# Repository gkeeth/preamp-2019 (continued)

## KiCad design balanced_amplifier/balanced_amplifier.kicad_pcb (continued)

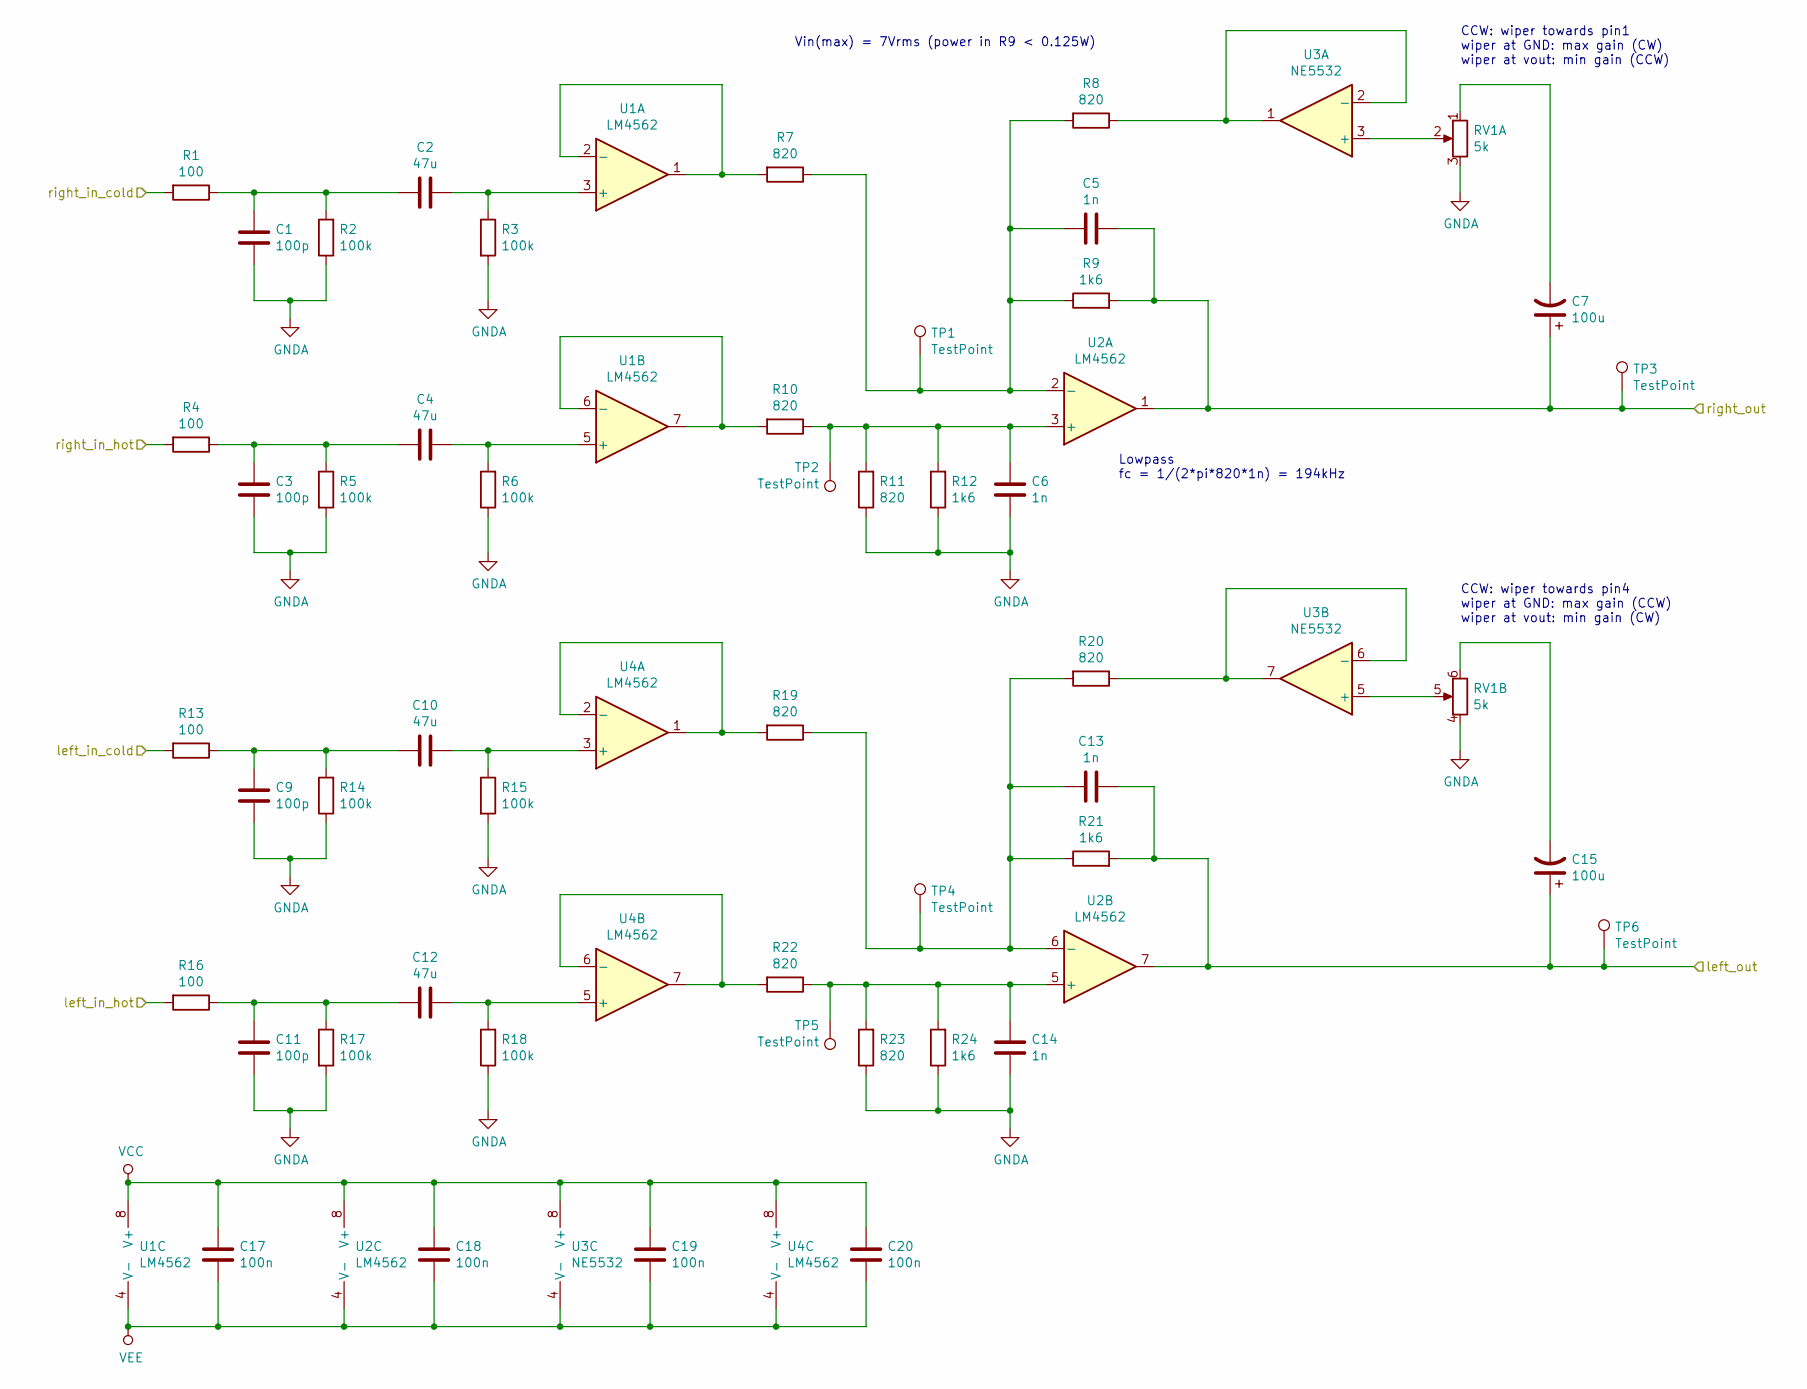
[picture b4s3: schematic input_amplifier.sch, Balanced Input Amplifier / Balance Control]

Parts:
C1, C3, C9, C11: 100p; C_0603_1608Metric_Pad1.05x0.95mm_HandSolder; Manufacturer PN CC0603JRNPO9BN101
C2, C4, C10, C12: 47u; C_Radial_D8.0mm_H11.5mm_P3.50mm; Voltage Rating 35V; Manufacturer PN UVP1V470MPD
C5, C6, C13, C14: 1n; C_0603_1608Metric_Pad1.05x0.95mm_HandSolder; Manufacturer PN GRM1885C1H102FA01J
C7, C15: 100u; CP_Radial_D6.3mm_P2.50mm; Voltage Rating 35V; Manufacturer PN UVR1V101MED
C17, C18, C19, C20: 100n; C_0805_2012Metric_Pad1.15x1.40mm_HandSolder; Manufacturer PN GCM21BR72A104KA37K
R1, R4, R13, R16: 100; R_0603_1608Metric_Pad1.05x0.95mm_HandSolder; Manufacturer PN RT0603FRE07100RL
R2, R3, R5, R6, R14, R15, R17, R18: 100k; R_0603_1608Metric_Pad1.05x0.95mm_HandSolder; Manufacturer PN AT0603DRD07100KL
R7, R8, R10, R11, R19, R20, R22, R23: 820; R_0603_1608Metric_Pad1.05x0.95mm_HandSolder; Manufacturer PN ERA-3AEB821V
R9, R12, R21, R24: 1k6; R_1206_3216Metric_Pad1.42x1.75mm_HandSolder; Manufacturer PN ERA-8AEB162V
RV1: 5k; Potentiometer_Bourns_91A2x-x28-xxx_Dual_Horizontal; Manufacturer PN 91A2A-B28-B13/B13L
TP1, TP2, TP3, TP4, TP5, TP6: TestPoint; TestPoint_Keystone_5000-5004_Miniature; Manufacturer PN 5002
U1, U2, U4: LM4562; SOIC-8_3.9x4.9mm_P1.27mm; Manufacturer PN LM4562MAX/NOPB
U3: NE5532; SOIC-8_3.9x4.9mm_P1.27mm; Manufacturer PN NE5532AD8R2G

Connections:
/left_in_cold: R13.2; also elsewhere on the board
/left_in_hot: R16.2; also elsewhere on the board
/right_in_cold: R1.2; also elsewhere on the board
/right_in_hot: R4.2; also elsewhere on the board
/volume_control/left_in: C13.1, C15.1, R21.2, TP6.1, U2.7; also elsewhere on the board
/volume_control/right_in: C5.1, C7.1, R9.2, TP3.1, U2.1; also elsewhere on the board
GNDA: C1.2, C3.2, C6.2, C9.2, C11.2, C14.2, R2.1, R3.2, R5.2, R6.1, R11.1, R12.1, R14.1, R15.2, R17.2, R18.1, R23.1, R24.1, RV1.3, RV1.4; also elsewhere on the board
unnamed: C1.1, C2.2, R1.1, R2.2
unnamed: C2.1, R3.1, U1.3 (+)
unnamed: C3.1, C4.2, R4.1, R5.1
unnamed: C4.1, R6.2, U1.5 (+)
unnamed: C5.2, R7.1, R8.2, R9.1, TP1.1, U2.2 (-)
unnamed: C6.1, R10.1, R11.2, R12.2, TP2.1, U2.3 (+)
unnamed: C7.2, RV1.1
unnamed: C10.1, R15.1, U4.3 (+)
unnamed: C9.1, C10.2, R13.1, R14.2
unnamed: C11.1, C12.2, R16.1, R17.1
unnamed: C12.1, R18.2, U4.5 (+)
unnamed: C13.2, R19.1, R20.2, R21.1, TP4.1, U2.6 (-)
unnamed: C14.1, R22.1, R23.2, R24.2, TP5.1, U2.5 (+)
unnamed: C15.2, RV1.6
unnamed: R7.2, U1.1, U1.2 (-)
unnamed: R8.1, U3.1, U3.2 (-)
unnamed: R10.2, U1.6 (-), U1.7
unnamed: R19.2, U4.1, U4.2 (-)
unnamed: R20.1, U3.6 (-), U3.7
unnamed: R22.2, U4.6 (-), U4.7
unnamed: RV1.2, U3.3 (+)
unnamed: RV1.5, U3.5 (+)
VCC: C17.1, C18.1, C19.1, C20.1, U1.8 (V+), U2.8 (V+), U3.8 (V+), U4.8 (V+); also elsewhere on the board
VEE: C17.2, C18.2, C19.2, C20.2, U1.4 (V-), U2.4 (V-), U3.4 (V-), U4.4 (V-); also elsewhere on the board

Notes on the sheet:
Lowpass fc = 1/(2*pi*820*1n) = 194kHz
CCW: wiper towards pin1 wiper at GND: max gain (CW) wiper at vout: min gain (CCW)
CCW: wiper towards pin4 wiper at GND: max gain (CCW) wiper at vout: min gain (CW)
Vin(max) = 7Vrms (power in R9 < 0.125W)

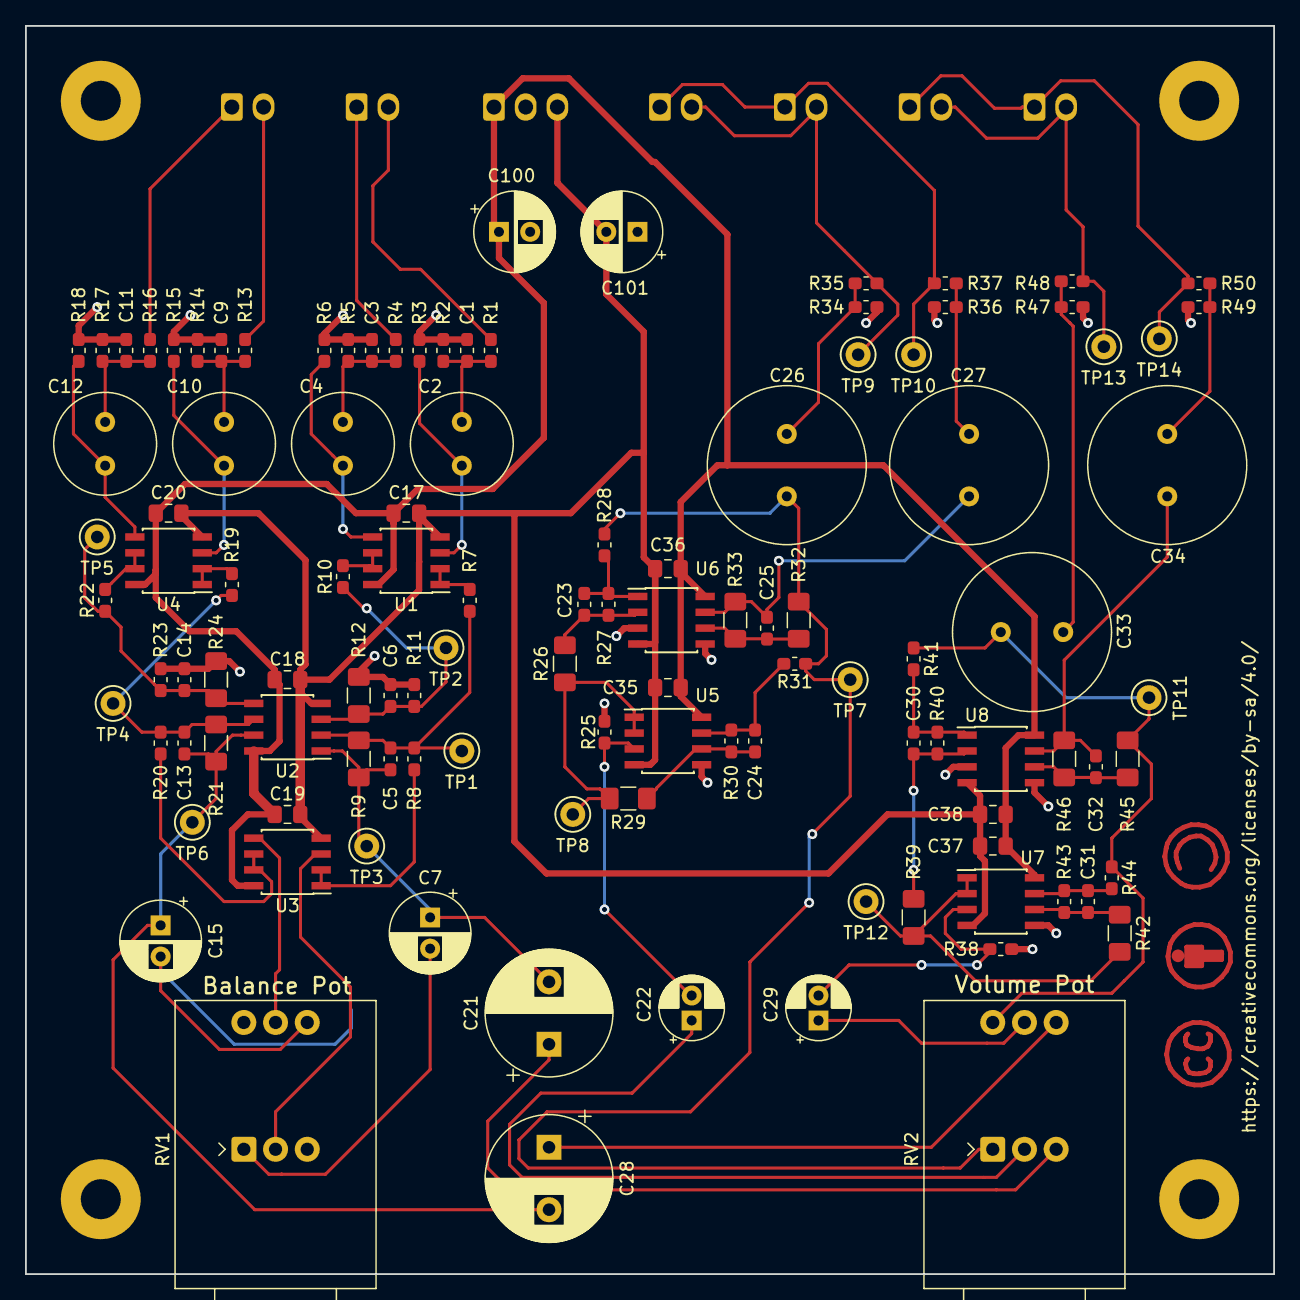
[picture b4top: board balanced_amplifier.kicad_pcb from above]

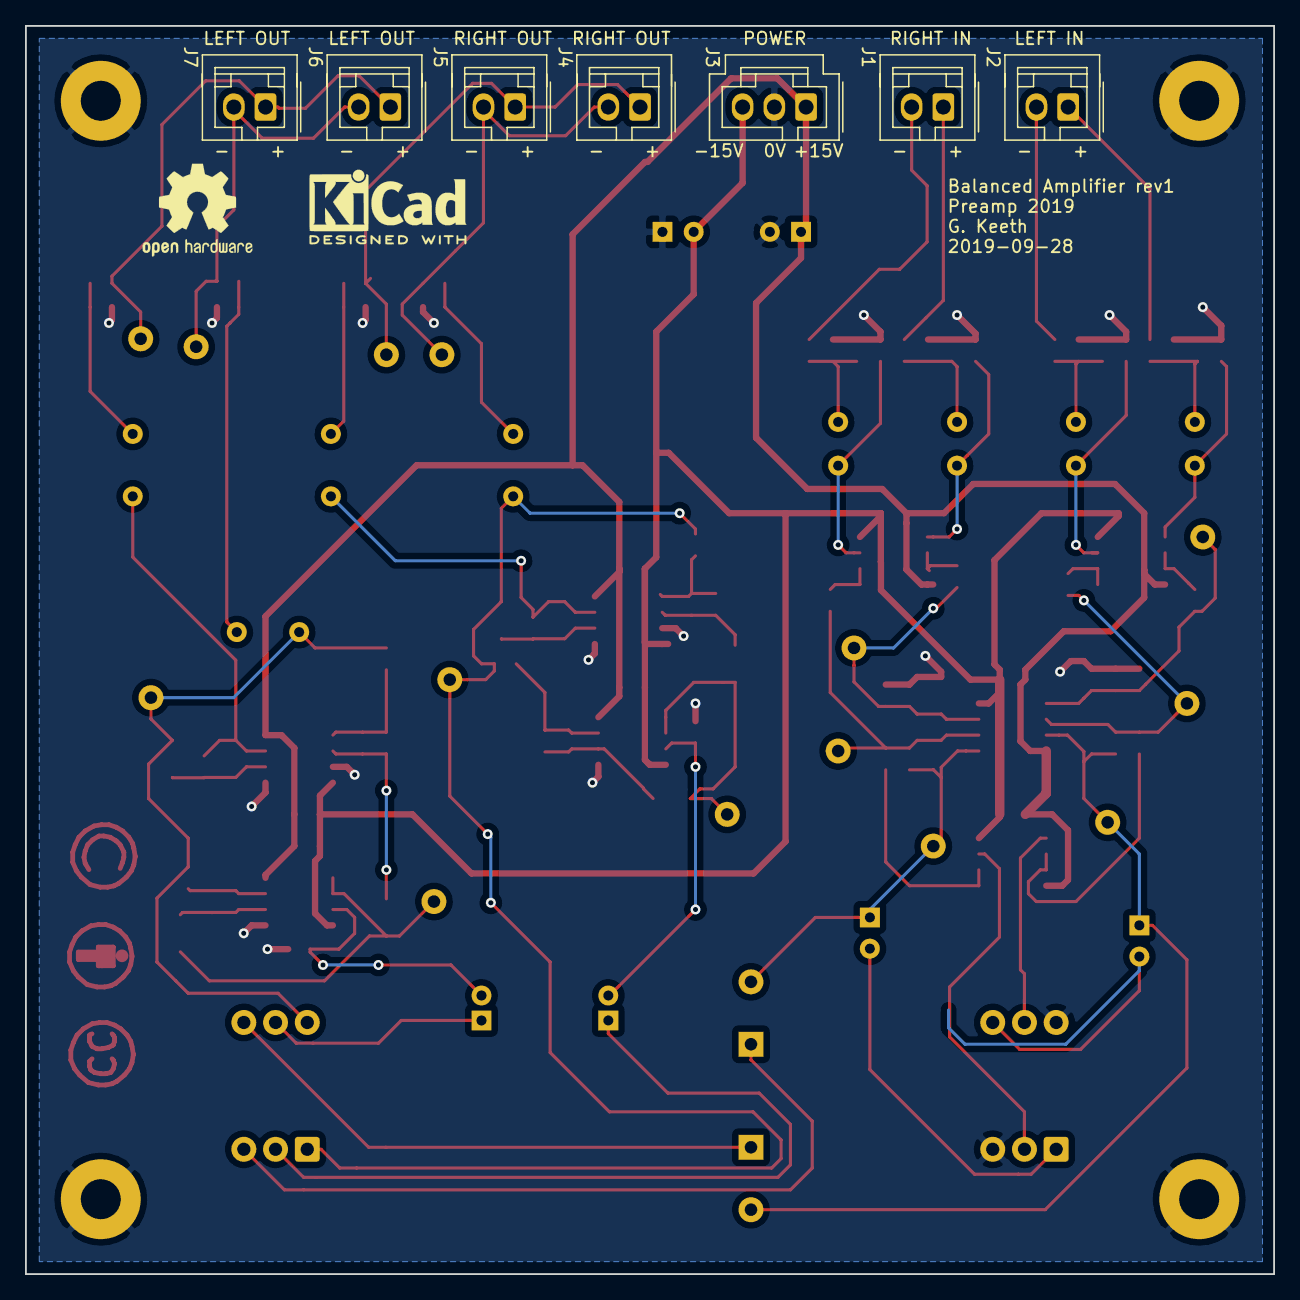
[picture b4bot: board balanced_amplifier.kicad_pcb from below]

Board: 2 copper layers, 100.0 x 100.0 mm, 123 parts (7 on the bottom side), 61 nets.

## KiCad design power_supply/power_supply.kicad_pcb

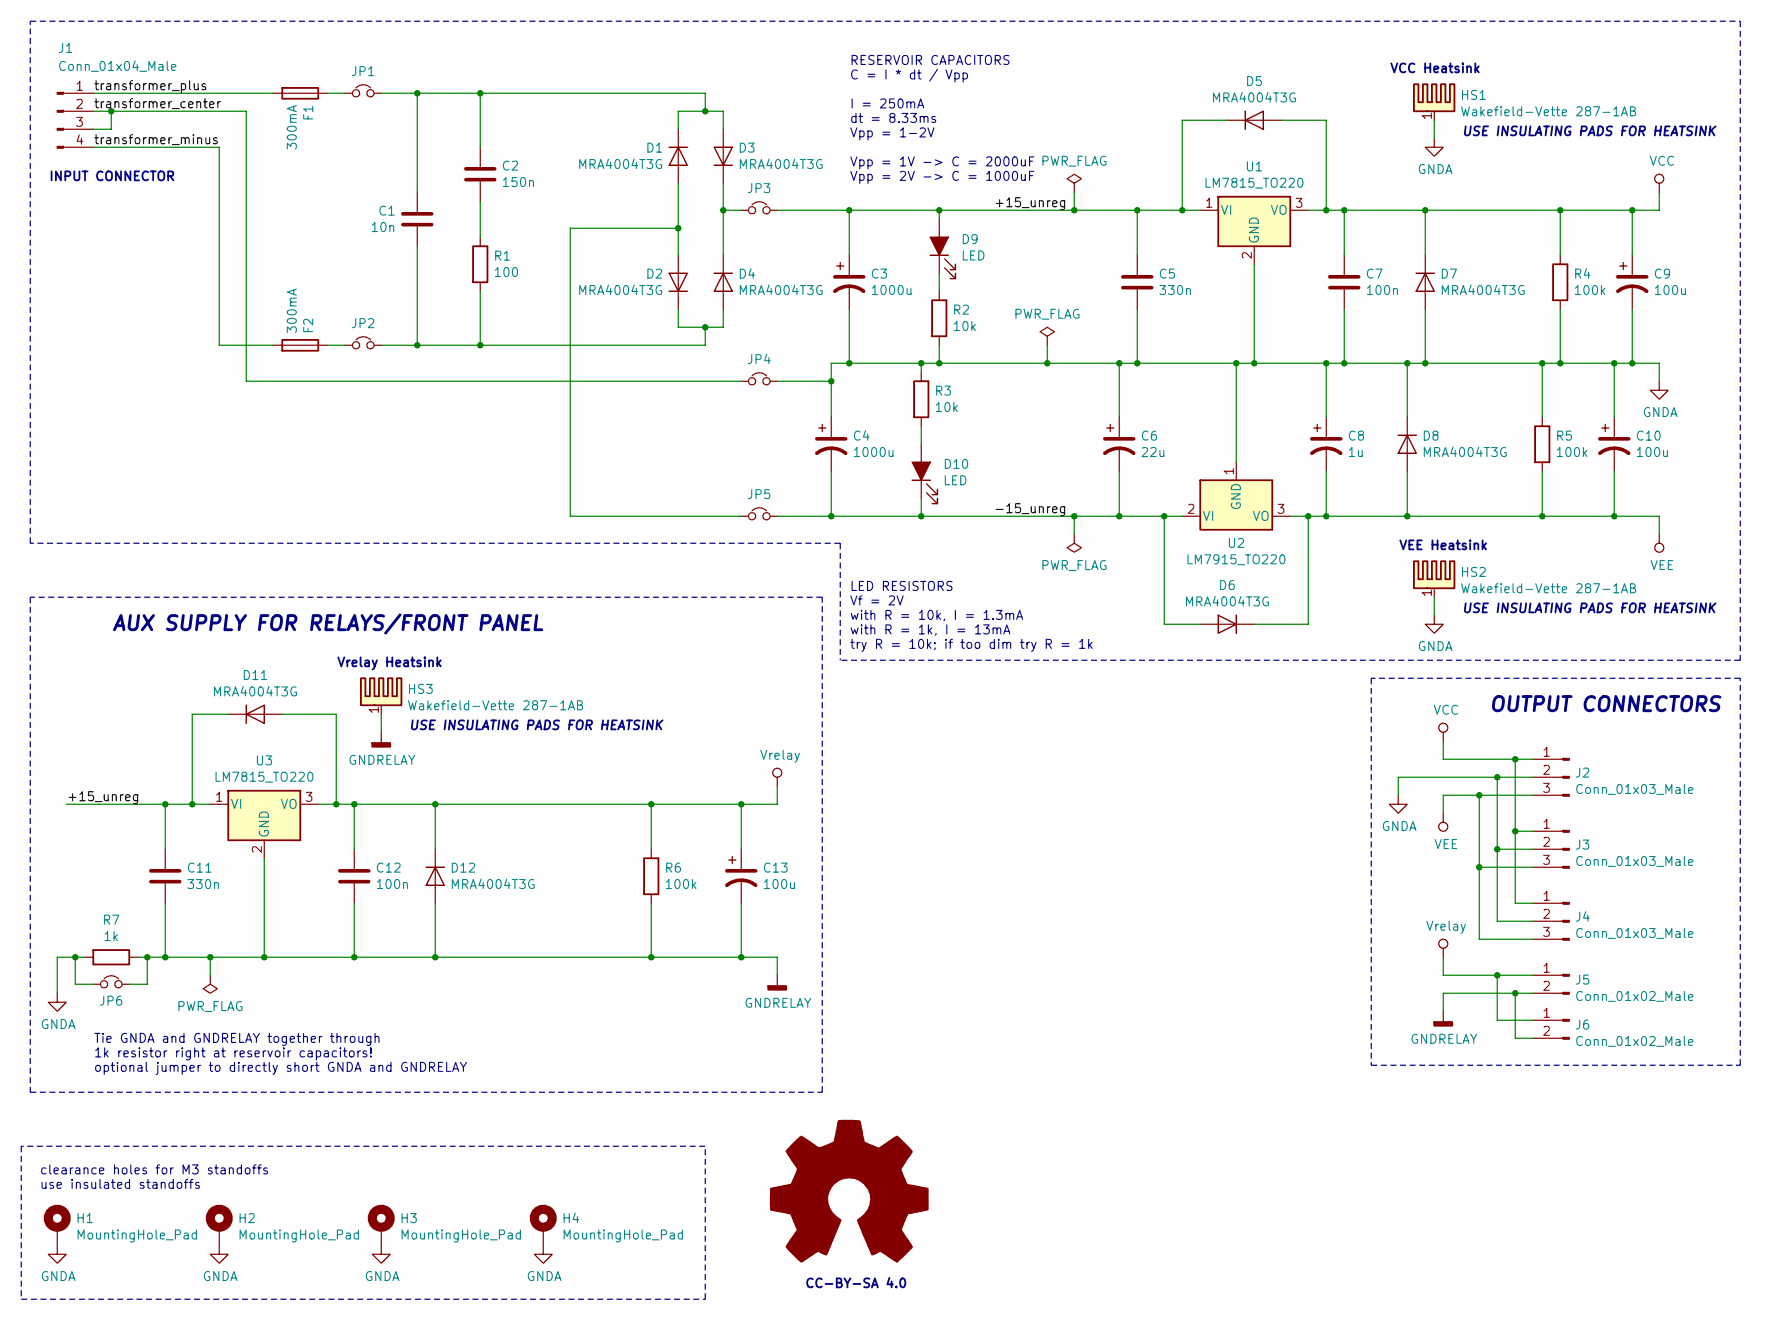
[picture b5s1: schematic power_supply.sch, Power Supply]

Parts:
C1: 10n; C_Rect_L7.2mm_W2.5mm_P5.00mm_FKS2_FKP2_MKS2_MKP2; Manufacturer PN B32529C3103J000
C2: 150n; C_Rect_L7.5mm_W6.5mm_P5.00mm; Manufacturer PN B32529C3154K000
C3, C4: 1000u; CP_Radial_D12.5mm_P5.00mm; Manufacturer PN UHE1H102MHD
C5, C11: 330n; C_0805_2012Metric_Pad1.15x1.40mm_HandSolder; Manufacturer PN CL21B334KBFNNNE
C6: 22u; CP_Radial_D5.0mm_P2.00mm; Manufacturer PN UHE1H220MDD
C7, C12: 100n; C_0805_2012Metric_Pad1.15x1.40mm_HandSolder; Manufacturer PN CL21B104MBCNNNC
C8: 1u; CP_Radial_D4.0mm_P1.50mm; Manufacturer PN UMT1H010MDD1TP
C9, C10, C13: 100u; CP_Radial_D6.3mm_P2.50mm; Manufacturer PN UVZ1V101MED1TD
D1, D2, D3, D4, D5, D6, D7, D8, D11, D12: MRA4004T3G; D_SMA; Manufacturer PN MRA4004T3G
D9, D10: LED; LED_0603_1608Metric; Manufacturer PN LTST-C191KRKT
F1, F2: 300mA; Fuseholder_Cylinder-5x20mm_Schurter_0031_8201_Horizontal_Op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; Manufacturer PN 0031.8201
H1, H2, H3, H4: MountingHole_Pad; MountingHole_3.2mm_M3_Pad
HS1, HS2, HS3: Wakefield-Vette 287-1AB; Heatsink_Wakefield-Vette_287-1AB_TO-220_Vertical; Manufacturer PN 287-1ABE
J1: Conn_01x04_Male; Molex_KK-396_A-41791-0004_1x04_P3.96mm_Vertical; Manufacturer PN 026614040
J2, J3, J4: Conn_01x03_Male; Molex_SL_A-70543-0002_1x03_P2.54mm_Vertical; Manufacturer PN 705430002
J5, J6: Conn_01x02_Male; Molex_SL_A-70543-0001_1x02_P2.54mm_Vertical; Manufacturer PN 705430001
JP1, JP2, JP3, JP4, JP5, JP6: Jumper_NC_Small; PinHeader_1x02_P2.54mm_Vertical
R1: 100; R_1206_3216Metric_Pad1.42x1.75mm_HandSolder; Manufacturer PN RT1206FRE07100RL
R2, R3: 10k; R_0603_1608Metric_Pad1.05x0.95mm_HandSolder; Manufacturer PN RT0603FRE0710KL
R4, R5, R6: 100k; R_0603_1608Metric_Pad1.05x0.95mm_HandSolder; Manufacturer PN RT0603FRE07100KL
R7: 1k; R_0603_1608Metric_Pad1.05x0.95mm_HandSolder; Manufacturer PN RT0603FRE071KL
U1, U3: LM7815_TO220; TO-220-3_Vertical; Manufacturer PN L7815ABV
U2: LM7915_TO220; TO-220-3_Vertical; Manufacturer PN L7915ACV

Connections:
/+15_unreg: C3.1, C5.1, C11.1, D5.1 (K), D9.2 (A), D11.1 (K), JP3.2, U1.1 (VI), U3.1 (VI)
/-15_unreg: C4.2, C6.2, D6.2 (A), D10.1 (K), JP5.2, U2.2 (VI)
/transformer_center: J1.2, J1.3, JP4.1
/transformer_minus: F2.2, J1.4
/transformer_plus: F1.2, J1.1
GNDA: C3.2, C4.1, C5.2, C6.1, C7.2, C8.1, C9.2, C10.1, D7.2 (A), D8.1 (K), H1.1, H2.1, H3.1, H4.1, HS1.1, HS2.1, J2.2, J3.2, J4.2, JP4.2, JP6.1, R2.2, R3.1, R4.2, R5.1, R7.2, U1.2 (GND), U2.1 (GND)
GNDRELAY: C11.2, C12.2, C13.2, D12.2 (A), HS3.1, J5.2, J6.2, JP6.2, R6.2, R7.1, U3.2 (GND)
unnamed: C1.1, C2.1, D1.1 (K), D3.2 (A), JP1.2
unnamed: C1.2, D2.1 (K), D4.2 (A), JP2.2, R1.2
unnamed: C2.2, R1.1
unnamed: D1.2 (A), D2.2 (A), JP5.1
unnamed: D3.1 (K), D4.1 (K), JP3.1
unnamed: D9.1 (K), R2.1
unnamed: D10.2 (A), R3.2
unnamed: F1.1, JP1.1
unnamed: F2.1, JP2.1
VCC: C7.1, C9.1, D5.2 (A), D7.1 (K), J2.1, J3.1, J4.1, R4.1, U1.3 (VO)
VEE: C8.2, C10.2, D6.1 (K), D8.2 (A), J2.3, J3.3, J4.3, R5.2, U2.3 (VO)
Vrelay: C12.1, C13.1, D11.2 (A), D12.1 (K), J5.1, J6.1, R6.1, U3.3 (VO)

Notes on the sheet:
LED RESISTORS Vf = 2V with R = 10k, I = 1.3mA with R = 1k, I = 13mA try R = 10k; if too dim try R = 1k
RESERVOIR CAPACITORS C = I * dt / Vpp I = 250mA dt = 8.33ms Vpp = 1-2V Vpp = 1V -> C = 2000uF Vpp = 2V -> C = 1000uF
clearance holes for M3 standoffs use insulated standoffs
OUTPUT CONNECTORS
INPUT CONNECTOR
USE INSULATING PADS FOR HEATSINK
Tie GNDA and GNDRELAY together through 1k resistor right at reservoir capacitors! optional jumper to directly short GNDA and GNDRELAY
AUX SUPPLY FOR RELAYS/FRONT PANEL
VCC Heatsink
VEE Heatsink
Vrelay Heatsink
CC-BY-SA 4.0

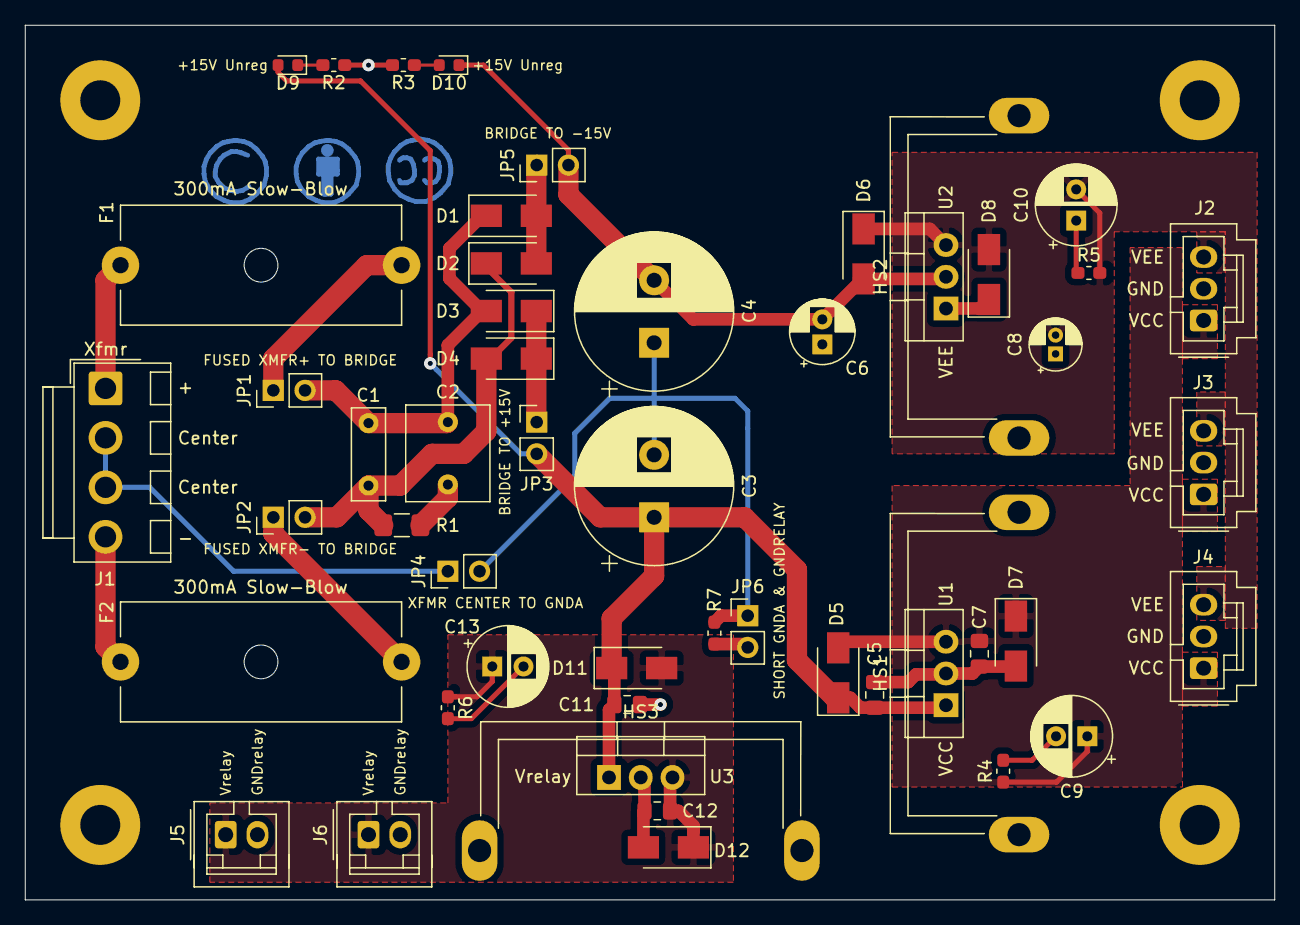
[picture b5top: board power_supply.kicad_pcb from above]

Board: 2 copper layers, 100.0 x 70.0 mm, 56 parts (0 on the bottom side), 19 nets.

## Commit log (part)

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2018-11-17 Update output coupling cap to be nonpolarized and add specific part details
2018-11-17 add specific part details to capacitors
2018-11-18 specify resistor details
2018-11-19 Add connectors to root sheet. Connector footprints may need to be changed
2018-11-20 swap hot and cold inputs to preserve overall phase
2018-11-27 Update TODO comment
2018-12-11 Add .gitignore
2018-12-11 Remove *.bak files (now ignored)
2018-12-15 Add testpoints
2018-12-15 Add power flags, run DRC
2018-12-15 Add netlist
2018-12-15 Initial import of netlist to pcb. Missing footprints for nonpolarized electrolytics
2018-12-15 Add footprints for unpolarized electrolytics
2018-12-15 Initial placement of footprints
2018-12-16 Update page layout
2018-12-17 Initial layout of input amplifier (incomplete)
2018-12-17 complete initial layout of input section
2018-12-17 initial placement of volume control circuits
2018-12-20 chamfer corners of VCC/VEE fills
2018-12-20 Adjust refdes positions
2018-12-20 Update TODO list
2018-12-20 add mounting holes to layout
2018-12-20 Update TODO list (mounting holes added to PCB)
2018-12-20 Add schematic annotation for hole size
2018-12-21 Add models for potentiometers
2018-12-21 Add models for 4-pin molex connectors
2018-12-21 ignore .stp files
2018-12-21 add 3d models for testpoints
2018-12-21 ignore .STEP files
2018-12-21 adjust reference designators
2018-12-31 Add fab (gerber) outputs
2018-12-31 Update date on schematics
2018-12-31 update project file
2018-12-31 Updated gitignore to ignore balanced amplifier bom dir
2019-01-11 Remove extraneous comment
2019-01-11 Update footprint for C21, C28
2019-01-11 Update PCB to fix rev0 issues
    - update C21/C28 footprint, re-route
    - swap pin 1/3, 4/6 on RV2 (volume pot) so turning CW increases volume
2019-01-15 Update TODO
2019-01-15 Create empty power supply
2019-01-15 Add components to power supply & update TODO
2019-01-18 Update TODO (add LEDs)
2019-01-18 Add notes.txt to record possible components to purchase
2019-03-24 Update some values and connections
2019-03-24 Update notes.txt with power inlet and power switch info
2019-03-24 Update TODO (current measurement headers)
2019-03-26 Update power supply schematic
    add jumpers for measuring current
    remove redundant capacitors
    wire LEDs
2019-03-28 add many component details & footprints to power supply
2019-03-28 change input connector to 1x4 Molex SL
2019-03-28 add note to change input bypass cap on 7915 to larger electrolytic
2019-03-30 Tidy schematic, add additional snubber capacitor
2019-03-31 update capacitors: add second pair of reservoir caps (DNP) and change input cap to 7915
2019-03-31 update footprints for mounting holes (8-32 clearance)
2019-03-31 update power supply schematic to move diodes before regulators
2019-03-31 update gitignore to ignore libreoffice spreadsheet lock files
2019-03-31 redraw output connectors on power supply
2019-04-07 add aux (relay/front panel power supply) to schematics/pcb. Also cleanup DRC violations in schematic
2019-04-07 add mostly empty front panel board project
2019-04-07 update title block for input/output board
2019-04-09 add input/output connectors and relays to schematic
2019-04-16 update TODO on balanced amp (headphone output)
2019-04-16 update TODO on front panel board (headphone amp)
2019-04-16 Update testpoint footprints on balanced amp board (revert 3dmodel to library default)
2019-04-18 add flyback diodes to relays
2019-04-18 add no-connect flags to NC relay terminals
2019-04-18 add output relay
2019-04-20 redraw input jack/relay circuits
2019-04-21 reorganize schematic and add graphic organization
2019-04-21 update balanced amplifier todo -- which ground to connect mounting holes to?
2019-04-25 re-save input output board schematic to fix schematic corruption (KiCad 5.1.1 bug, fixed in 5.1.2)
2019-04-27 update TODO and add footprint for relay control connector
2019-04-27 initial component placement for input/output board components
2019-04-27 add net classes. NOTE: relay footprints do not match schematic
2019-04-27 update relay footprints with fixed numbering
2019-04-27 update relay placement
2019-04-28 fix DRC error and move board on page. NOTE: several items left in TODO
2019-04-28 update schematic TODO
2019-05-02 update power symbols (add relay power&ground)
2019-05-02 add input selection switch to notes
2019-05-04 change input selection switch to 12-pos with adjustable stops
2019-05-07 complete schematic except footprint for output mute switch
2019-05-11 update chassis grounding in input/output board because jacks connect directly to chassis
2019-05-11 add better input selection switch (fewer positions, bigger angle) and link for output jack
2019-05-12 add footprint for toggle switch and do inital layout (exact switch/LED placement tbd)
2019-06-01 update todo for input output board
2019-06-01 update heatsinks in schematic
2019-06-01 continued preliminary placement
2019-06-03 complete most initial layout
2019-06-06 beautify schematic, update TODO, and tweak LEDs
2019-06-06 complete basic layout, add silkscreen labels, add all models, update TODO
2019-06-07 add OSHW/license to schematic
2019-06-08 update text, and finalize damping resistor value
2019-06-08 hide text for mounting holes
2019-06-08 change CC license version in schematic text from 3 to 4
2019-06-08 change floating PCB text to footprint text
2019-06-08 move graphic symbols off-board temporarily and update TODO
2019-06-08 remove extra reservoir caps from layout and move remaining once to new location
2019-06-08 redesign input/output capacitors for regulators and add bleeder resistors on output caps
2019-06-08 correct silkscreen text for jumper JP6 based on schematic reannotation
2019-06-09 update electrolytic capacitors to 105C models
2019-06-09 complete routing, including planes, thickening traces, and silkscreen labels
2019-06-09 remove TODO (completed) from schematic
2019-06-10 move regulators w.r.t. heatsinks to match ST 7x15 package
2019-06-10 reposition fab text
2019-06-10 update date field in layout and schematic sheet headers
2019-06-10 add gerbers and pdf of schematic and layout
2019-06-10 update project info on silk label
2019-06-10 update project silk info in layout pdf
2019-06-10 update TODO for input/output board
2019-06-10 add bom for power supply. Some component fields empty (not all parts mapped to actual MFNs)
2019-06-10 update balanced amplifier TODO and swap power connector for molex SL
2019-06-11 change footprints for R4-6 to a resistor 0603 instead of capacitor 0603
2019-06-11 update gerbers and layout pdf with R4-6 footprint correction and new project rev
2019-06-12 update rotary switch footprint again
2019-06-17 remove shield from internal audio connectors, change internal audio connectors to 1x2, and split input shields into four separate nets (one for each input)
2019-06-18 update balanced amplifier TODO
2019-06-18 update TODO and title block
2019-06-19 update balanced amplifier layout for connector changes
2019-06-19 adjust mounting hole placement and dimensioning
2019-06-19 update TODO and date in titleblock
2019-06-19 resize project info silk, update date
2019-06-19 update title block
2019-06-22 add jumpers to schematic to optionally bypass output relay. Update TODO. Clean up schematic
2019-06-22 add connector to bypass mute switch and change rotary switch to 8pos model
2019-06-22 change GNDD to GNDRELAY
2019-06-23 annotate graphic symbols and new power ports in schematic
2019-06-23 update switch symbol/footprint, add second relay control connector, and re-layout (LED not laid out)
2019-06-24 update footprint for volume/balance pots
2019-06-27 add labels to connectors
2019-06-29 update Molex SL footprints from library
2019-07-11 rename board in README
2019-09-10 update TODO and add license comment
2019-09-10 add sch-bak files to gitignore
2019-09-14 Complete initial schematic for headphone amplifier
    Features present:
    - left and right channels
    - input connectors, output jack
    - balanced-to-unbalanced converters
    - power connector
    - bulk capacitance
2019-09-14 add all footprints
2019-09-14 update input output board for headphone amp connections
2019-09-14 change connectors to be horizontal, and add initial *rough* placement of parts to layout
2019-09-17 update schematic & layout so output connector is same as input connectors
2019-09-19 update output transistor symbols/footprints
2019-09-21 change output transistors to std lib versions (now in upstream)
2019-09-21 update schematic symbols to NCJ6FA-H-0 (no release tab), update footprints to project-local versions
2019-09-21 update jack footprints in layout to project-local footprints from upstream pull request
2019-09-21 add project fp-lib-table
2019-09-22 finalize layout based on schematic. Add silk/fab labels to connectors
2019-09-22 update net labelling, change to SPDT switch for headphone selection, and clean up schematic
2019-09-22 initial layout for headphone amplifier. Still need to finalize mounting orientation and adjust connectors/mounting holes if necessary
2019-09-22 adjust output connector location slightly
2019-09-22 update todo (add reminder to consider switching to horizontal connectors)
2019-09-22 update README with revised project info and license
2019-09-22 Rename LICENSE.md to LICENSE.txt
2019-09-22 insert fancy markdown for license in README
2019-09-22 remove shield from README
2019-09-26 Remove output resistors
    - remove output resistors for zero ohm output impedance
    - add 10k pulldown/bleeder resistors on output to prevent output cap
    charging with no load
2019-09-26 add license info to TODO
2019-09-27 update output cap footprint and bleeder resistor
    - update output cap footprint (20mm height vs 25mm to match actual part)
    - increase bleeder resistor value to 22k from 10k, to decrease corner
    frequency
2019-09-27 move pots to be 60mm apart
2019-09-27 clean up fab labels and silkscreen
2019-09-27 connect output jack ground to star point with net tie
2019-09-28 move pots 1mm further beyond board edge
2019-09-28 correct transformer part number
2019-09-28 add info silk to headphone amplifier
2019-09-28 Finalize layout for rev1
    - switch to smaller M3 holes
    - move input/output/power connectors to bottom of board for better
    accessibility in enclosure
    - change power planes to simple traces. Planes were unnecessary.
2019-09-28 change to M3 mounting holes
2019-09-29 update TODO list with chassis mount jack
2019-09-29 remove TODO from input/output schematic -- not adding pulldown resistors to main output
2019-09-30 change relay resistors to 0805 and label headphone switch
2019-09-30 generate fab outputs for complete prototype
2019-10-01 add BOMs for front panel board, headphone amp, and input/output board
2019-10-01 enter all BOM info
2019-10-01 fill out all input/output board BOM info
2019-10-01 generate new BOM with all distributor info
2019-10-01 complete all BOM info
2019-10-13 fix schematic/routing of headphone relay (reverse coil polarity)
2019-10-13 update sheet date, revision, and board silkscreen
    Update sheet info/silk to give today's date and rev1
2019-10-13 update gitignore to ignore interactive HTML bom files
2019-10-13 generate rev1 headphone amp gerbers
2019-10-13 update headphone amp BOM for rev1
2019-10-13 regenerate gerbers for rev1 input/output board
2019-12-14 git update input/output gerber zip with r1 gerbers
2019-12-16 update input output board to use a right-angle relay connector (requiring renumbering of connector pins)
2019-12-16 replot input/output board (r2)
2019-12-16 plot gerbers for rev1 front panel board
